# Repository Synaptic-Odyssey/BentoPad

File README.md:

# BentoPad

The 4 white keycaps will be the "rice", one rotary encoder will be a sushi and the other will be an
eggroll. Combined with the 3d printed pork katsu, after painting the macropad will look like a bento box!

**Overall Hackpad**  

**Schematic**  

**PCB**  

**Assembly (done with superglue)**  

**BOM:**  
- Seeed XIAO RP2040
- 4x MX-Style switches
- 2x EC11 Rotary encoders
- 4x Blank DSA keycaps (White)

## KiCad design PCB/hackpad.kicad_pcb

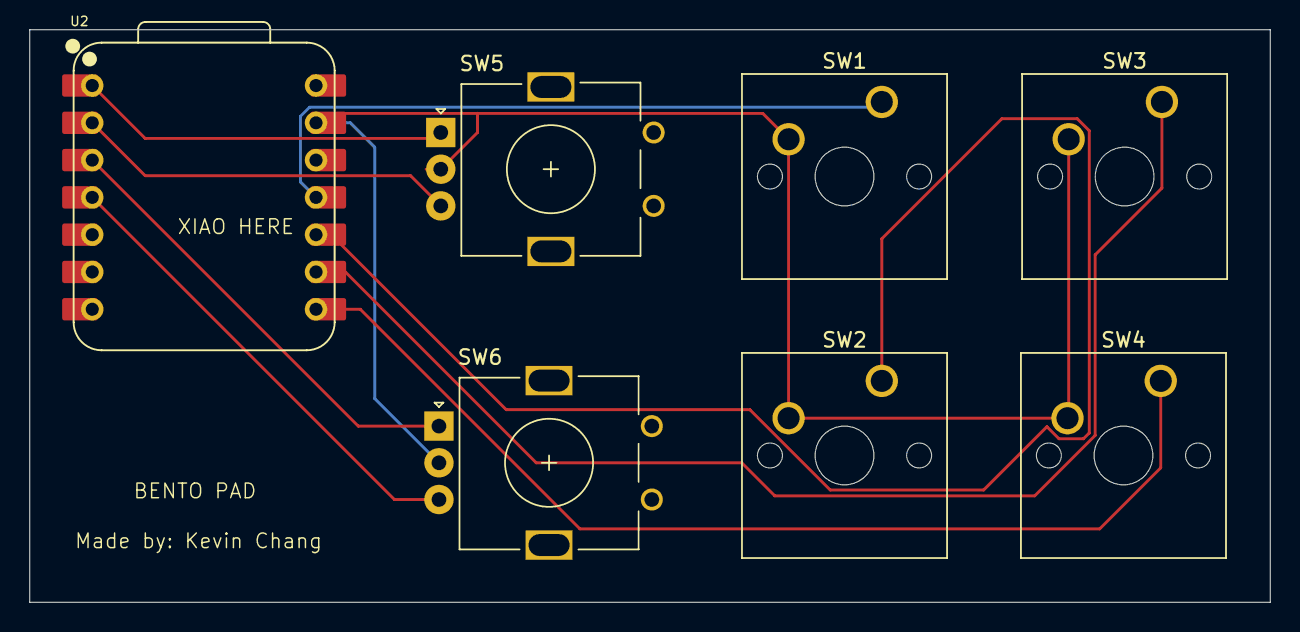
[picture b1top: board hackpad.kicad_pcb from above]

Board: 2 copper layers, 84.5 x 39.0 mm, 7 parts (0 on the bottom side), 9 nets.

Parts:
SW1, SW2, SW3, SW4: SW_Push; SW_Cherry_MX_1.00u_PCB
SW5, SW6: RotaryEncoder; RotaryEncoder_Alps_EC11E_Vertical_H20mm
U2: XIAO-RP2040-DIP

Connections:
END1A: SW5.A, U2.1 (GPIO26/ADC0/A0)
END1B: SW5.B, U2.2 (GPIO27/ADC1/A1)
END2A: SW6.A, U2.3 (GPIO28/ADC2/A2)
END2B: SW6.B, U2.4 (GPIO29/ADC3/A3)
GND: SW1.2, SW2.2, SW3.2, SW4.2, SW5.C, SW6.C, U2.13 (GND)
SW1: SW1.1, U2.11 (GPIO3/MOSI)
SW2: SW2.1, U2.10 (GPIO4/MISO)
SW3: SW3.1, U2.9 (GPIO2/SCK)
SW4: SW4.1, U2.8 (GPIO1/RX)

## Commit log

2025-06-18 finished
2025-06-18 readme update
2025-06-18 ordered images
2025-06-18 quick fix
